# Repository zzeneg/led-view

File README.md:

# led-view
nice!view drop-in repacement with a single LED

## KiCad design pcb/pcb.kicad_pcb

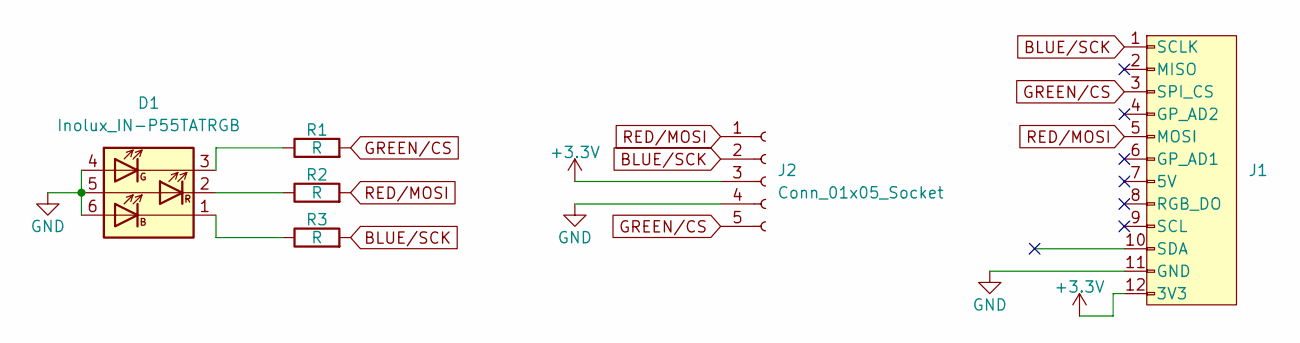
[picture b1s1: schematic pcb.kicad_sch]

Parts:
D1: Inolux_IN-P55TATRGB; LED_RGB_5050-6-flip
J1: vik-module-connector; Connector_VIK-horizontal-module
J2: Conn_01x05_Socket; PinSocket_1x05_P2.54mm_Vertical
R1, R2, R3: R; R_1206_3216Metric_Pad1.30x1.75mm_HandSolder

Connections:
+3.3V: J1.12 (3V3), J2.3
BLUE/SCK: J1.1 (SCLK), J2.2, R3.2
GND: D1.4 (AG), D1.5 (AR), D1.6 (AB), J1.11 (GND), J2.4
GREEN/CS: J1.3 (SPI_CS), J2.5, R1.2
unnamed: D1.1 (KB), R3.1
unnamed: D1.3 (KG), R1.1
unnamed: D1.2 (KR), R2.1
RED/MOSI: J1.5 (MOSI), J2.1, R2.2

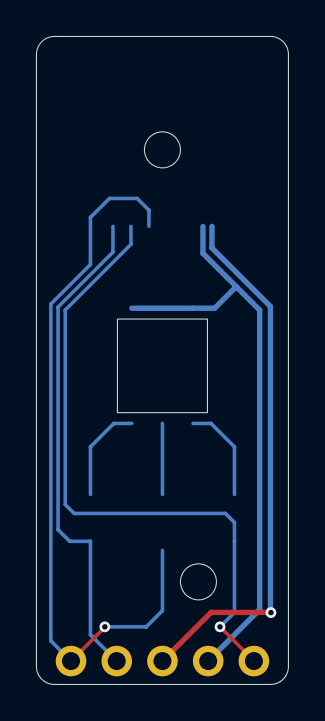
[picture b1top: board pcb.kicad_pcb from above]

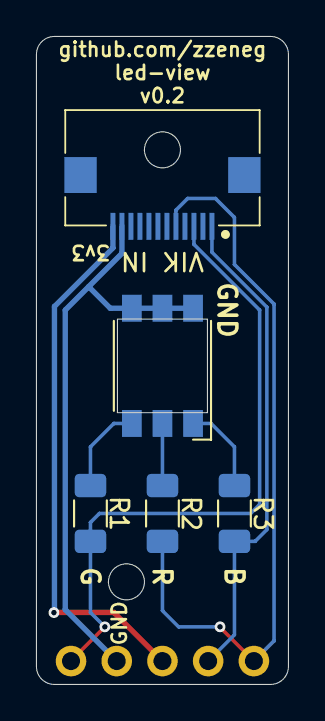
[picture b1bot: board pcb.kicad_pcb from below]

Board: 2 copper layers, 14.0 x 36.0 mm, 6 parts (4 on the bottom side), 8 nets.

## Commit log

2024-12-27 first release
2025-01-15 support VIK adapter
